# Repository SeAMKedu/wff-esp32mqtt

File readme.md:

[seamk_logo]:       /img/seamk_logo.svg
[epliitto_logo]:    /img/epliitto_logo.jpg
[eakr_eu_logo]:     /img/eakr_eu_logo.jpg

# Analogia signaalit pilveen

Ruokalaboratorion homogenisaattorissa on valmiit liitännät, joista voi lukea 4-20mA signaalin paineantureista. Tässä repositoryssä on kuvattu ESP32 pohjainen lähetin, joka osaa lukea nämä signaalit ja lähettää ne edelleen MQTT viesteinä eteenpäin. 

## Piirilevy

PCB kansiosta löytyy KiCAD piirustukset sovittimesta, johon voi laittaa ESP32 Dev Kitin kiinni sekä kytkeä 24V virran ja kaksi mA-signaalia. HUOM! Tämä on laajempaa jakelua varten piirretty uudelleen KiCADilla, eikä sitä ole testattu. Testattu prototyyppi tehtiin EasyEDAlla mikä on hieman rajattu yhteen piirilevyvalmistajaan. KiCAD versiossa on myös lisätty OneWire liitäntä lämpötila-anturia varten, mikä ei ole käytössä ohjelmassa.

## Ohjelma

Ohjelma ESP32:lle tietojen lähettämistä varten on kirjoitettu PlatformIO ympäristössä. Asenna se ja avaa projekti. `platformio.ini` tiedostossa on muuttujat WIFI-verkon ja MQTT palvelimen asetuksille. Aseta sinne itsellesi sopivat arvot.

## Wise Frami Food hanke

Tämä ohjelma luotiin osana Wise Frami Food hanketta, jossa rakennettiin piloitointiympäristö Frami Food Labin yhteyteen.

![eakr_eu_logo] 

---

![epliitto_logo]

---

![seamk_logo]

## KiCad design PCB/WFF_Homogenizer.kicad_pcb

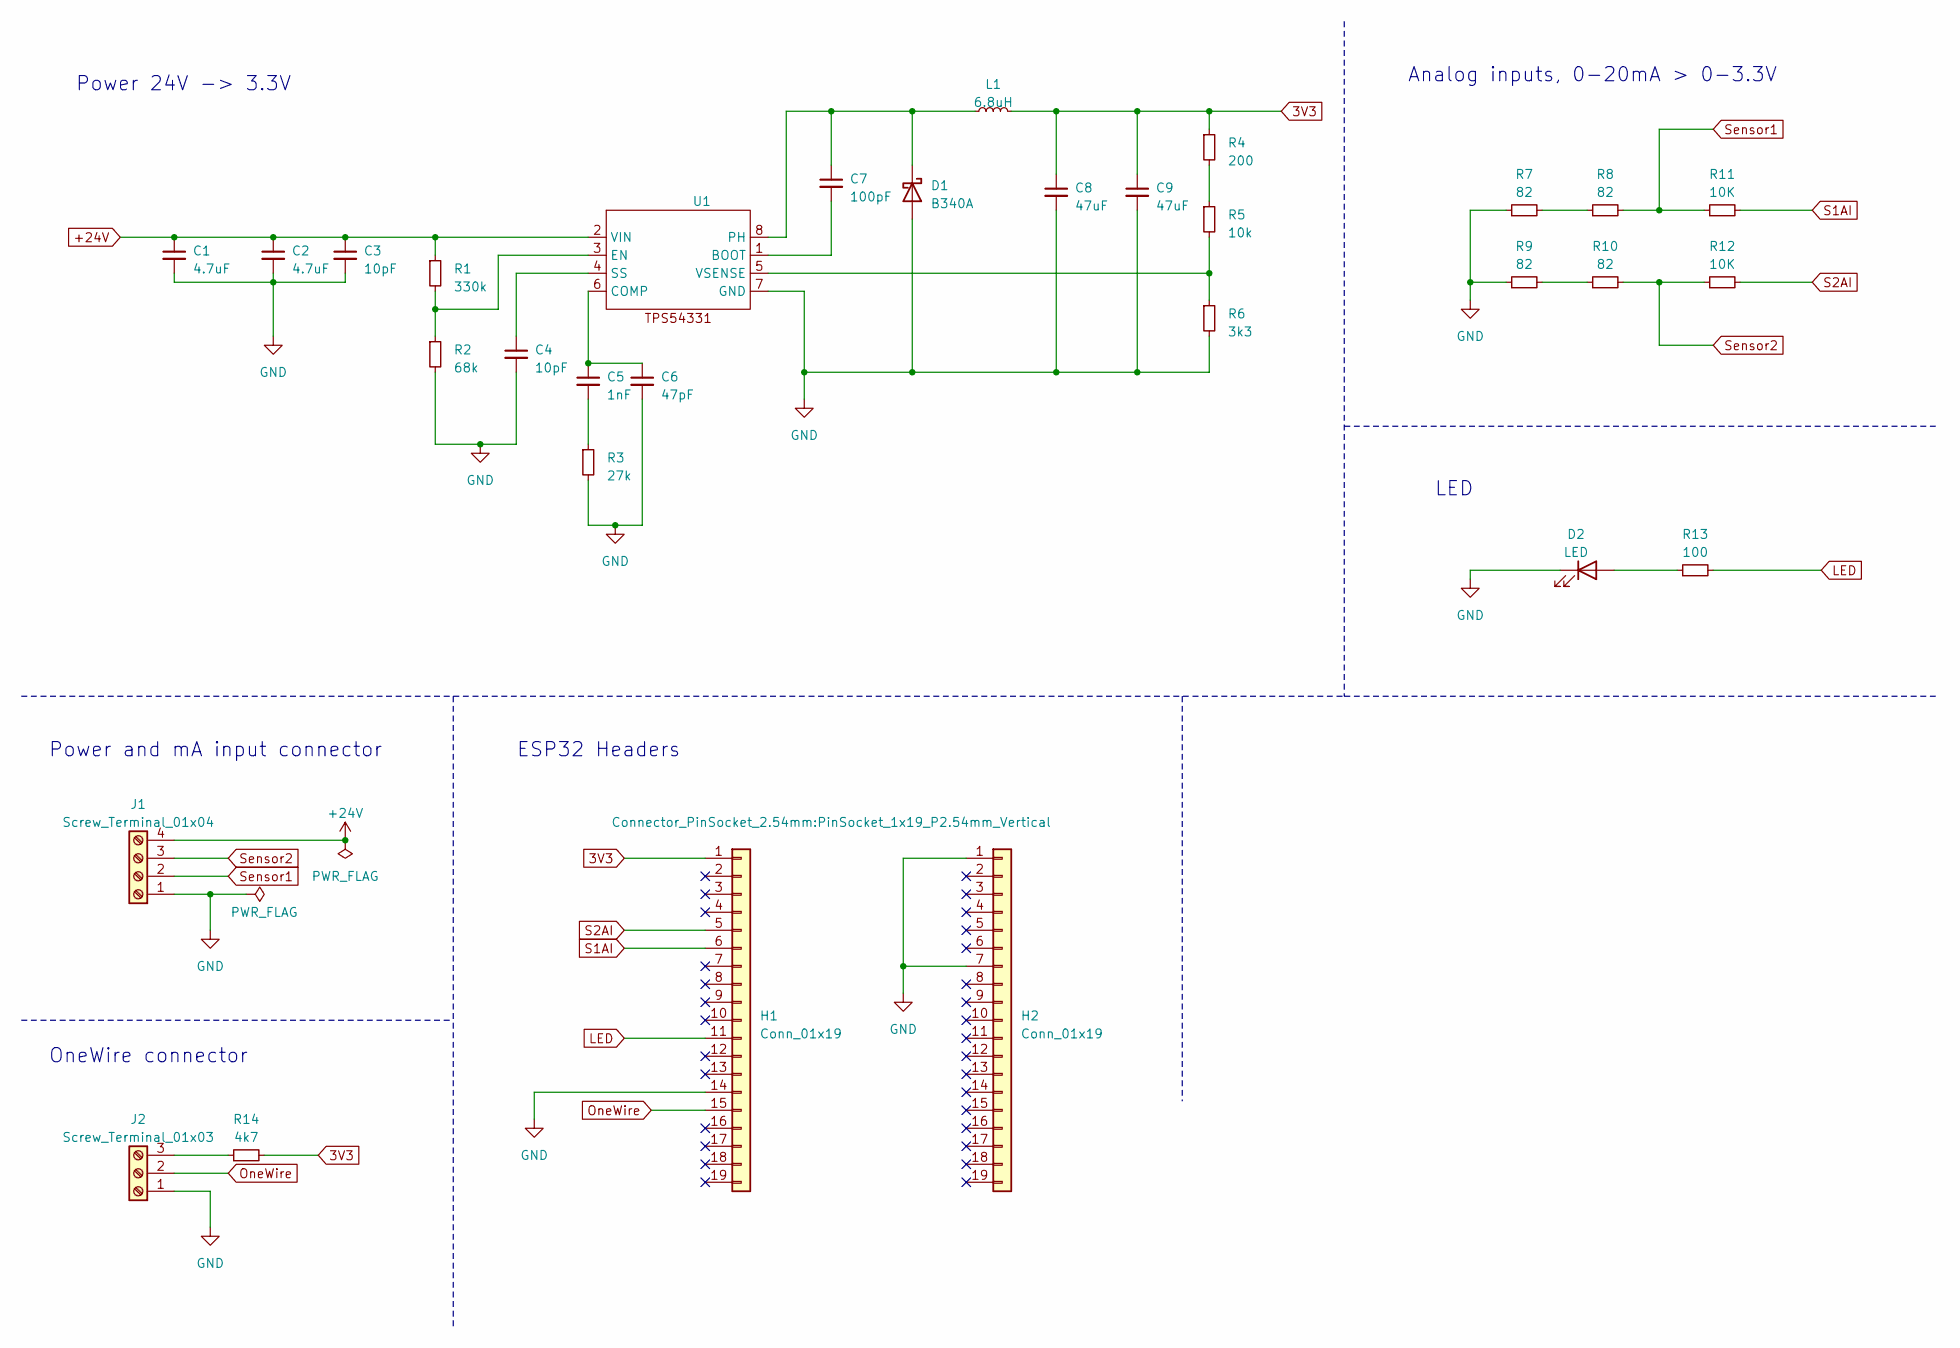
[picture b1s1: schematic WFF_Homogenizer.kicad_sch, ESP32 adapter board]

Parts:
C1, C2: 4.7uF; C_0603_1608Metric
C3, C4: 10pF; C_0603_1608Metric
C5: 1nF; C_0603_1608Metric
C6: 47pF; C_0603_1608Metric
C7: 100pF; C_0603_1608Metric
C8, C9: 47uF; C_0603_1608Metric
D1: B340A; D_SMA
D2: LED; LED_0603_1608Metric
H1, H2: Conn_01x19; PinSocket_1x19_P2.54mm_Vertical
J1: Screw_Terminal_01x04; TerminalBlock_Phoenix_MKDS-1,5-4_1x04_P5.00mm_Horizontal
J2: Screw_Terminal_01x03; TerminalBlock_Phoenix_MKDS-1,5-3_1x03_P5.00mm_Horizontal
L1: 6.8uH; L_6.3x6.3_H3
R1: 330k; R_0603_1608Metric
R2: 68k; R_0603_1608Metric
R3: 27k; R_0603_1608Metric
R4: 200; R_0603_1608Metric
R5: 10k; R_0603_1608Metric
R6: 3k3; R_0603_1608Metric
R7, R8, R9, R10: 82; R_0603_1608Metric
R11, R12: 10K; R_0603_1608Metric
R13: 100; R_0603_1608Metric
R14: 4k7; R_0603_1608Metric
U1: TPS54331DR SOIC-8

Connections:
3V3: C8.1, C9.1, H1.1, L1.2, R4.1, R14.2
+24V: C1.1, C2.1, C3.1, J1.4, R1.1, U1.2 (VIN)
GND: C1.2, C2.2, C3.2, C4.2, C6.2, C8.2, C9.2, D1.2 (A), D2.1 (K), H1.14, H2.1, H2.7, J1.1, J2.1, R2.2, R3.2, R6.2, R7.1, R9.1, U1.7 (GND)
LED: H1.11, R13.2
unnamed: C5.2, R3.1
unnamed: C7.1, D1.1 (K), L1.1, U1.8 (PH)
unnamed: D2.2 (A), R13.1
unnamed: J2.3, R14.1
unnamed: R4.2, R5.1
unnamed: R7.2, R8.1
unnamed: R9.2, R10.1
unnamed: C7.2, U1.1 (BOOT)
unnamed: C5.1, C6.1, U1.6 (COMP)
unnamed: R1.2, R2.1, U1.3 (EN)
unnamed: C4.1, U1.4 (SS)
unnamed: R5.2, R6.1, U1.5 (VSENSE)
OneWire: H1.15, J2.2
S1AI: H1.6, R11.2
S2AI: H1.5, R12.2
Sensor1: J1.2, R8.2, R11.1
Sensor2: J1.3, R10.2, R12.1

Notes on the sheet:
Analog inputs, 0-20mA > 0-3.3V
ESP32 Headers
Power and mA input connector
OneWire connector
LED
Power 24V -> 3.3V

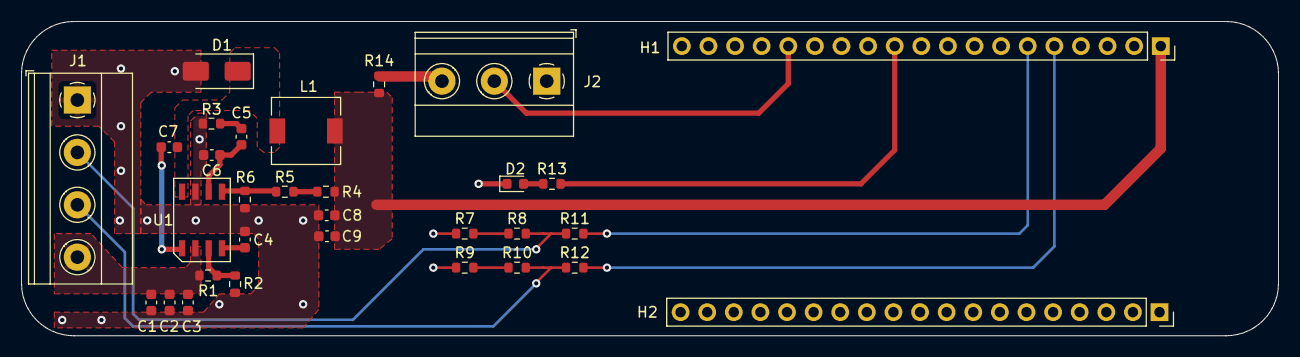
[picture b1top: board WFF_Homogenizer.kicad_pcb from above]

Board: 2 copper layers, 120.0 x 30.0 mm, 31 parts (0 on the bottom side), 21 nets.

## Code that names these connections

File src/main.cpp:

#include <Arduino.h>
#include <ArduinoJson.h>
#include <WiFi.h>
#include <PubSubClient.h>
#include <OneWire.h>
#include <DallasTemperature.h>

#define LED         27
#define AN_Sensor1  34
#define AN_Sensor2  35
#define ONEWIRE     25

// https://www.esp32.com/viewtopic.php?t=13053

uint8_t temprature_sens_read();
void setup_wifi();
void callback(char* topic, byte* message, unsigned int length);
void readAnalogValues();

const char* clientName = CLIENT_NAME;
const char* topicInput = TOPIC_INPUT;
const char* topicOutput = TOPIC_OUTPUT;
const char* ssid = WIFI_SSID;
const char* password = WIFI_PASSWORD;
const char* mqtt_server = MQTT_SERVER;
const char* mqtt_user = MQTT_USERNAME;
const char* mqtt_passwd = MQTT_PASSWORD;
const int adcAt4mA = ADC_AT4MA;
const int adcAt20mA = ADC_AT20MA;
const int sensorMin = ADC_MIN;                      // 0 bar
const int sensorMax = ADC_MAX;                   // 1000 bar
const uint8_t numReadings = 16;
const uint8_t numSensors = 4;
uint32_t readings[numSensors][numReadings];   // multi-dimensional readings from analog input
uint32_t readIndex = 0;                       // the index of the current reading
uint32_t total[numSensors] = {0};             // the running total
uint32_t average = 0;                         // the average

// interval to stabilize analog input smoothing readings
// ADC1 Channel read time ~9.5µs per sample --> 64 readings x 9.5 = 608 µs = .608 ms
uint8_t numReadingsInterval = 2;
uint32_t numReadingsStart = 0;

WiFiClient espClient;
PubSubClient client(espClient);

OneWire oneWire(ONEWIRE);
DallasTemperature sensors(&oneWire);
int numberOfDevices;
DeviceAddress tempDeviceAddress; 

long lastMsg = 0;
char msg[50];
int value = 0;
int sensor1value = 0;
int sensor2value = 0;
bool ledOn = false;

void setup() {
  Serial.begin(115200);

  pinMode(LED, OUTPUT);

  analogReadResolution(12);
  analogSetWidth(12);
  analogSetAttenuation(ADC_11db);
  adcAttachPin(AN_Sensor1);
  adcAttachPin(AN_Sensor2);

  // initialize all the readings to 0
  for (uint8_t thisReading = 0; thisReading < numReadings; thisReading++) {
    for ( uint8_t j = 0; j < numSensors; j++)  readings[j][thisReading] = 0;
  }

  setup_wifi();

  client.setServer(mqtt_server, 1883);
  client.setCallback(callback);

  numberOfDevices = sensors.getDeviceCount();
}

void setup_wifi() {
  delay(10);
  // We start by connecting to a WiFi network
  Serial.println();
  Serial.print("Connecting to ");
  Serial.println(ssid);

  WiFi.begin(ssid, password);

  while (WiFi.status() != WL_CONNECTED) {
    delay(500);
    Serial.print(".");

    if (ledOn) {
      digitalWrite (LED, LOW);
      ledOn = false;
    } else {
      digitalWrite (LED, HIGH);
      ledOn = true;
    }
  }

  digitalWrite (LED, HIGH);
  ledOn = true;

  Serial.println("");
  Serial.println("WiFi connected");
  Serial.print("IP address: ");
  Serial.println(WiFi.localIP());
}

void callback(char* topic, byte* message, unsigned int length) {
  Serial.print("Message arrived on topic: ");
  Serial.print(topic);
  Serial.print(". Message: ");
  String messageTemp;
  
  for (int i = 0; i < length; i++) {
    Serial.print((char)message[i]);
    messageTemp += (char)message[i];
  }
  Serial.println();
}

void reconnect() {
  // Loop until we're reconnected
  while (!client.connected()) {
    digitalWrite (LED, HIGH);
    Serial.print("Attempting MQTT connection...");
    // Attempt to connect
    if (client.connect(clientName, mqtt_user, mqtt_passwd)) {
    //if (client.connect(clientName)) {
      Serial.println("connected");
      digitalWrite (LED, LOW);
      // Subscribe
      client.subscribe(topicInput);
    } else {
      Serial.print("failed, rc=");
      Serial.print(client.state());
      Serial.println(" try again in 5 seconds");
      // Wait 5 seconds before retrying
      delay(5000);
    }
  }
}

void readAnalogValues() {
  // Read the sensor
  uint16_t sensor1 = analogRead(AN_Sensor1);
  uint16_t sensor2 = analogRead(AN_Sensor2);
  uint16_t inputPin[numSensors] = { sensor1, sensor2 };

  for (uint8_t ai = 0; ai < numSensors ; ai++) {
    total[ai] = total[ai] - readings[ai][readIndex];  // remove previous value from total
    readings[ai][readIndex] = inputPin[ai];           // store current value
    total[ai] = total[ai] + readings[ai][readIndex];  // add current to total
  }

  // advance index or loop around
  readIndex = readIndex + 1;
  if (readIndex >= numReadings) {
    readIndex = 0;
  }

  // calculate average from total
  sensor1value = total[0] / numReadings;
  sensor2value = total[1] / numReadings;
}

void loop() {
  if (!client.connected()) {
    reconnect();
  }

  client.loop();

  int hall = hallRead();
  // temperature sensor is not present
  //float temp = (temperatureRead() - 32 ) / 1.8;
  
  if (millis() - numReadingsStart >= numReadingsInterval * numReadings) {
    numReadingsStart = millis();
    readAnalogValues();
  }

  long now = millis();
  if (now - lastMsg >= 1000) {
    // led is on every other second
    ledOn = !ledOn;

    if (ledOn) {
      digitalWrite (LED, HIGH);
    } else {
      digitalWrite (LED, LOW);
    }

    //Serial.println("Temp: " + String(temp) + "C, hall: " + String(hall) + "C, S1: " + String(sensor1value) + "V, S2: " + String(sensor2value) + "V");
    //Serial.println("Hall: " + String(hall) + "C, S1: " + String(sensor1value) + ", " + String(sensor1Pressure) + " bar, S2: " + String(sensor2value) + ", " + String(sensor1Pressure) + " bar, [" + String(adcAt4mA) + ", " + String(adcAt20mA) + "]");

    lastMsg = now;
    //char tempString[8];
    //dtostrf(temp, 1, 2, tempString);

    char sensor1rawString[8];
    dtostrf(sensor1value, 1, 2, sensor1rawString);

    char sensor2rawString[8];
    dtostrf(sensor2value, 1, 2, sensor2rawString);

    char hallString[8];
    dtostrf(hall, 1, 2, hallString);

    DynamicJsonDocument json(300);
    
    json["hall"] = hallString;
    json["s1raw"] = sensor1rawString;
    json["s2raw"] = sensor2rawString;
 
    sensors.requestTemperatures();
    for(int i=0; i < numberOfDevices; i++) {
      if (sensors.getAddress(tempDeviceAddress, i)) {
        //float tempC = sensors.getTempC(tempDeviceAddress);
        json["temp" + i] = sensors.getTempC(tempDeviceAddress);
      }
    }

    char buffer[100];
    size_t n = serializeJson(json, buffer);
    
    if (client.publish(topicOutput, buffer, n) != true) {
      Serial.println("Error sending message");
    }
  }

  // no need to run too fast
  delay(50);
}

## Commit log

2023-12-31 MCU code
2023-12-31 KiCAD project and plot
2023-12-31 Kuvaus
2023-12-31 Create LICENSE
2024-02-20 Update readme.md with doi.
